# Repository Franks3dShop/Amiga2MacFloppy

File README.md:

# Amiga2MacFloppy
Amiga2MacFloppy, a reversed-engineered A-Max interface

Video of the project from Dr. Dave's Diversions channel, we did this project together:
https://youtu.be/zkYM3wdAgQM?t=42

# General Description

The original A-Max II software allowed to emulate a Macintosh computer on the Amiga and provided an interface (Figure 1) to connect an external Apple floppy drive and use it in emulation. It is also compatible with CrossMAC on the Amiga so you can read Mac floppies on the Amiga.

Amiga2MacFloppy (Figure 2) is a recreation of that board without the Mac ROMs that were required on the original board. It works all the same with a patched version of A-Max II so that it loads the ROMs from file instead.

This interface is designed to receive the IDC connector directly from a 3.5 inch Mac floppy drive or FloppyEmu. You also have the option to the DB19M to IDC adapter (Figure 3) to connect an external Mac floppy drive.

Figure 1-Amax II Interface

Figure 2: The Amiga2MacFloppy Interface

Figure 3 - Adapter DB19M to IDC 2x10

# Software Configuration

## CrossMAC

CrossMAC is Amiga software, consisting of device driver(s) and an
accompanying application, that allows the use of Mac HFS volumes
on the Amiga; the volumes can be mounted, read, and written. This
includes both Mac HFS-formatted 800KB floppy disks and SCSI-attached
Mac HFS hard drive partitions. For floppy disks, of course, some
hardware interface is required to connect the Amiga to a "classic"
Mac-compatible double density floppy drive; Amiga2MacFloppy is
that interface.

Amiga2MacFloppy is known to work with CrossMAC software v1.05 running
on Amiga Release 2.1 system software accompanied by either (a) the
FloppyEmu hardware emulator (in Mac floppy mode; *not* in HD20 mode),
(b) an Apple 3.5 inch double density floppy drive (external DB19
connector), or (c) a Cutting Edge branded 3.5 inch Mac-compatible
double density floppy drive (DB19 connector).

To use CrossMAC with an attached Amiga2MacFloppy, install the
CrossMAC software per its instructions.

## Using CrossMAC

Once CrossMAC installed successfully, HFS-formatted Mac floppy
disks should appear on the Amiga desktop when inserted and can
be accessed much like Amiga FFS volumes.  Launch the CrossMAC
application; this will display the HFS volumes current mounted
and provides Mac-specific HFS volume features such as ejecting
Mac floppy disks and specifying whether Mac HFS files should be
shown in Workbench having Both Forks, Data Fork, or MacBin Only.
split resource and forks.

If you do not have CrossMAC, you can
find it on archive.org in this set of
[CommodoreAmigaApplications](https://archive.org/details/CommodoreAmigaApplicationsADF).

## A-Max

A-Max is the first Macintosh emulator on the Amiga, introduced in
1989. A-Max takes over the entire Amiga when it is running, i.e. does
not multitask with Amiga applications. As such, A-Max II is unique,
amongst Mac emulators on Amiga, in that the entire Amiga is dedicated
to the Mac operations making it fast and highly compatible with
early Mac software when emulating a Macintosh Plus, for example.

Amiga2MacFloppy is known to work with A-Max II software version
2.5 having the "Fast A-Max" patch and running on Amiga Release
2.1 system sofware accompanied by a Mac Plus 128K ROM image file,
and either (a) the FloppyEmu hardware emulator (in Mac floppy mode;
*not* HD20 mode), (b) an Apple 3.5 inch double density floppy drive
(external DB19 connector), or (c) a Cutting Edge branded 3.5 inch
Mac-compatible double density floppy drive (DB19 connector).

To use A-Max II software with an attached Amiga2MacFloppy, you must
use a version of A-Max patched to read the Mac ROM image from a
file rather than from the (2) DIP ROMs that were required in the
original A-Max "cartridge" (an interface that connected to the
Amiga's external floppy disk port) that Amiga2MacFloppy replaces.

The "Fast A-Max" patch modifies the A-Max II software, such as
version 2.5, to read the ROM image from a file called "Mac_ROMs"
in the same directory as the patched A-Max executable. This file
has a format specific to the Fast A-Max patch, but it can be easily
created, e.g. from a 128KB Mac Plus ROMs image file used by other
Mac emulators.  The file simply has a special 32-bit (4 byte)
header; this header contains two 16-bit numbers. The first field
indicates the size of ROM image follows (0x75 for 128KB Mac Plus
ROMs); the second field indicates the drive number or position
where the hardware interface is installed.

For example, a Mac_ROMs image file might begin like this:

	$ hexdump Mac_ROMs |head -1
	0000000 7500 0500 1f4d 7281 4000 2a00 7500 0060
	        ^^^^ ^^^^ ^^^^^^^^^^^^^^^^^^^^^^^^^^^^^
		|    |    |
		|    |    Mac [128KB] ROM image begins here
		|    |
		|    drive number (16-bit value, low byte first) here
		|
		Indicates 128KB (Mac Plus) ROM image follows

Typically, one might install the Amiga2MacFloppy as the second
drive, e.g. the first external drive on an Amiga 500, i.e. `df1:`,
if it were an Amiga floppy drive. In this case, the Mac ROM image
file should indicate the Mac floppy drive has the Amiga floppy drive
number of 4. That is, the ROM image file must specify drive number
4 like this:

	$ hexdump Mac_ROMs |head -1
	0000000 7500 0400 1f4d 7281 4000 2a00 7500 0060
	             ^^^^

Alternatively, one might install the Amgia2MacFloppy as the third
drive, e.g. the first external drive on an Amiga 2000 having two
internal 3.5 inch Amiga floppy drives, i.e. `df2:` if it were an
Amiga floppy drive. In this case, the Mac ROM image file should
indicate the Mac floppy drive has the Amiga floppy drive number of
5. That is the ROM image file must specify drive number 5 like this:

	$ hexdump Mac_ROMs |head -1
	0000000 7500 0500 1f4d 7281 4000 2a00 7500 0060
	             ^^^^

For your convenience, we can make available two Fast A-Max-compatible
ROM image files containing Mac Plus 128KB ROMs and configured
for either of those two floopy drive chain position options; see
Contact info [below](#contact). These are `Mac_ROMs_df1` and `Mac_ROMs_df2`
respectively and you just must copy (or rename) this to a file named
`Mac_ROMs` before starting A-Max II.

Aside: This unusual Mac ROM image file format is necessitated by
the Fast A-Max patch, not by Amiga2MacFloppy, per se. Since the
Fast A-Max patch replaces the portion of A-Max code that finds,
identifies, and loads the external ROMs, this special file header
is used by the patch code to store that necessary information and
convey it to the A-Max software so that A-Max knows the sort of Mac
ROMs supplied (either 64KB or 128KB) and also so that A-Max knows
how to locate the hardware interface to access floppy disks.

Note that if you change the number of Amiga floppy drives positioned
before the Amiga2MacFloppy interface, e.g. if you install an
additional Amiga floppy drive in an Amiga 2000, you will have to
change the Mac ROM image file to one in which the header reflects
the new device number/position of the Amiga2MacFloppy.

# Using A-Max

Most of the use of A-Max is outside the scope of this documentation.
Once properly configured, your Amiga2MacFloppy-connected device will
behave just like a external 800KB drive connected to a classic Mac.
You can even boot Macintosh System software from this external
floppy drive.

In our testing of A-Max II software version 2.5 having the Fast A-Max
patch, we have found no difference between using Amiga2MacFloppy and
using the original A-Max hardware interface. The rare incompatibility
with Macintosh software is likely due to the A-Max emulator, itself,
rather than the floppy drive interface. For example, the original
Microsoft Flight Simulator for the Macintosh is known not to work
with A-Max due to Flight Simulator's heinous requirement that the
original floppy disk must be installed in the internal Macintosh
floppy drive. However, the Mac-compatible floppy drive you attach
when using A-Max always appears as an external floppy drive, thus
it can't be used to run Flight Simulator.

# Dimensions

Figure 4: Dimensions of the Amiga2MacFloppy Board

# PCB Fabrication
You can get the board from PCBWay or any other manifacturer of your choice with the provided gerber zip files.
The default settings from PCBWay should be correct, I prefer to get "HASL lead free" boards to save on the environement https://www.pcbway.com/project/shareproject/Amiga2MacFloppy.html

# Assembly instructions
The PCB fits the 3D printed case provided, You have to center and push the DB23 connectors up to the board, try it first in the case before soldering.

# Revision History
Rev. 1
* Board cleaned up
* OpenHardware Logo added
* Remove the not needed resistor
* Added DB19 and DB23 reference files for KiCAD
* Tested and working

# Contact

Contact Dave via email at the address shared in the
Dr. Dave's Diversions YouTube channel's "About" info:
https://www.youtube.com/c/DrDavesDiversions/about

# LICENCE
©2021 Frank's 3D Shop & Dr. Dave's Diversions

<br />This work is licensed under a <a rel="license" href="http://creativecommons.org/licenses/by/4.0/">Creative Commons Attribution 4.0 International License</a>.

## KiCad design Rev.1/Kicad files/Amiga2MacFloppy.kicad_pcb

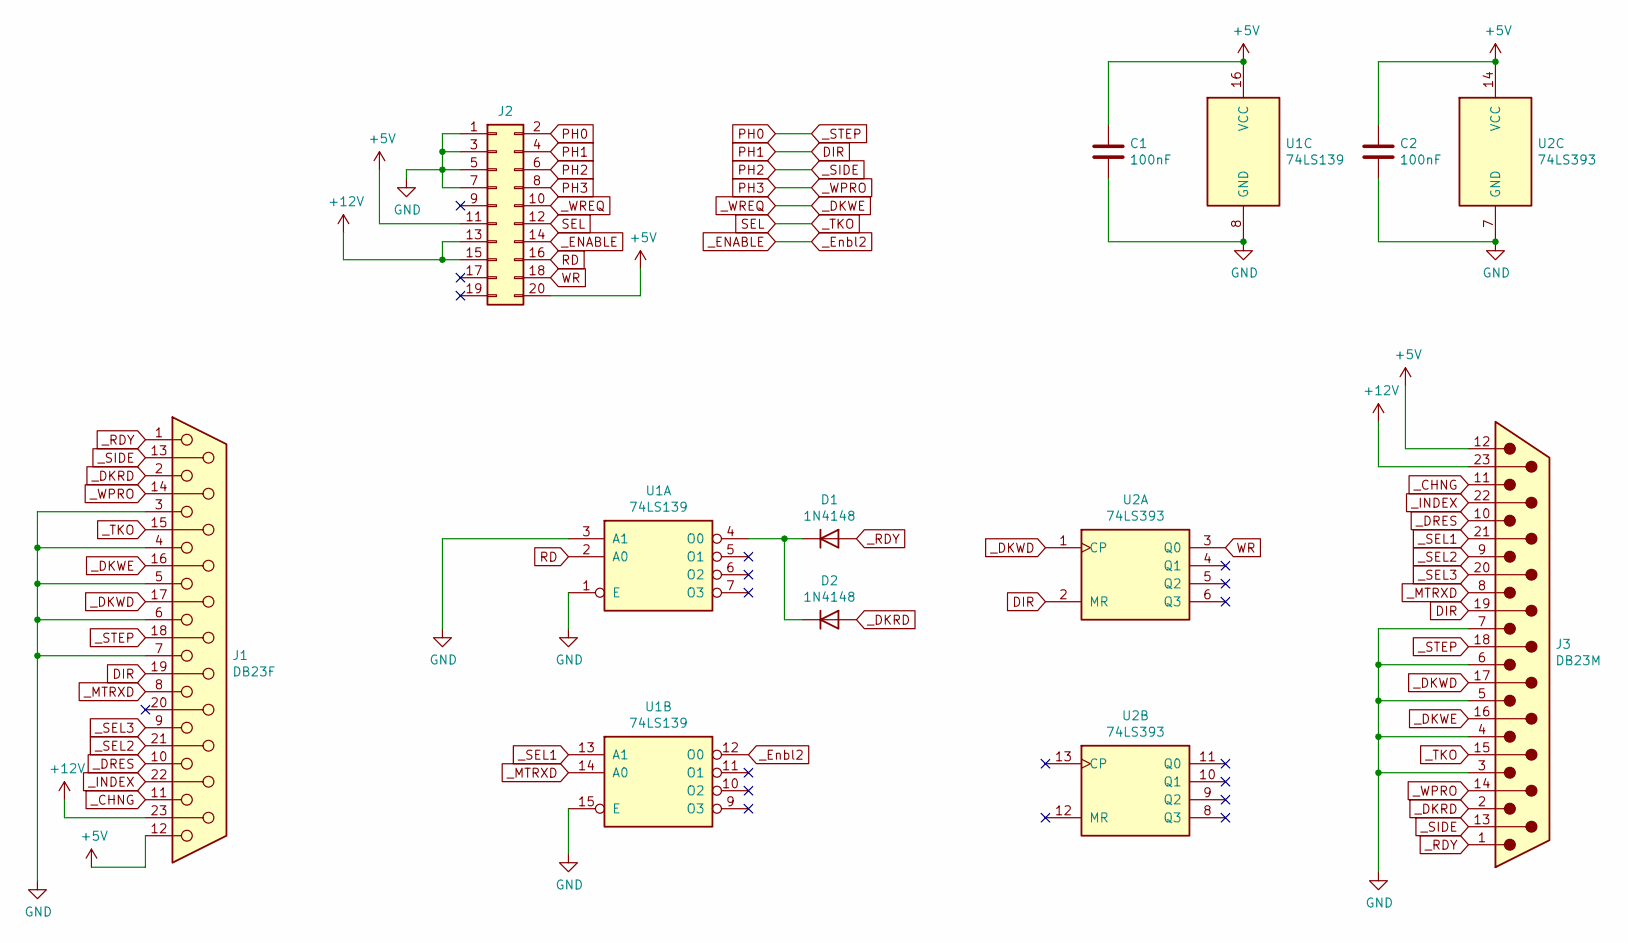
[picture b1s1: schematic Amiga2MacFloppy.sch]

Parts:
C1, C2: 100nF; C_Disc_D7.0mm_W2.5mm_P5.00mm
D1, D2: 1N4148; D_DO-35_SOD27_P7.62mm_Horizontal
J1: DB23F; DSUB-23_Female_EdgeMount_P2.77mm
J2: Conn_02x10_Odd_Even_MountingPin; IDC-Header_2x10_P2.54mm_Vertical
J3: DB23M; DSUB-23_Male_EdgeMount_P2.77mm
U1: 74LS139; DIP-16_W7.62mm
U2: 74LS393; DIP-14_W7.62mm

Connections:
+12V: J1.23, J2.13, J2.15, J3.23
DIR: J1.19, J2.4, J3.19, U2.2 (MR)
GND: C1.2, C2.2, J1.3, J1.4, J1.5, J1.6, J1.7, J2.1, J2.3, J2.5, J2.7, J3.3, J3.4, J3.5, J3.6, J3.7, U1.1 (E), U1.3 (A1), U1.8 (GND), U1.15 (E), U2.7 (GND); also elsewhere on the board
unnamed: D1.1 (K), D2.1 (K), U1.4 (O0)
PH0: J1.18, J2.2, J3.18
PH2: J1.13, J2.6, J3.13
PH3: J1.14, J2.8, J3.14
PWM: C1.1, C2.1, J1.12, J2.11, J2.20, J3.12, U1.16 (VCC), U2.14 (VCC)
RD: J2.16, U1.2 (A0)
SEL: J1.15, J2.12, J3.15
WR: J2.18, U2.3 (Q0)
_CHNG: J1.11, J3.11
_DKRD: D2.2 (A), J1.2, J3.2
_DKWD: J1.17, J3.17, U2.1 (CP)
_DKWE: J1.16, J2.10, J3.16
_DRES: J1.10, J3.10
_ENABLE: J2.14, U1.12 (O0)
_INDEX: J1.22, J3.22
_MTRXD: J1.8, J3.8, U1.14 (A0)
_RDY: D1.2 (A), J1.1, J3.1
_SEL1: J3.21, U1.13 (A1)
_SEL2: J1.21, J3.9; also elsewhere on the board
_SEL3: J1.9, J3.20

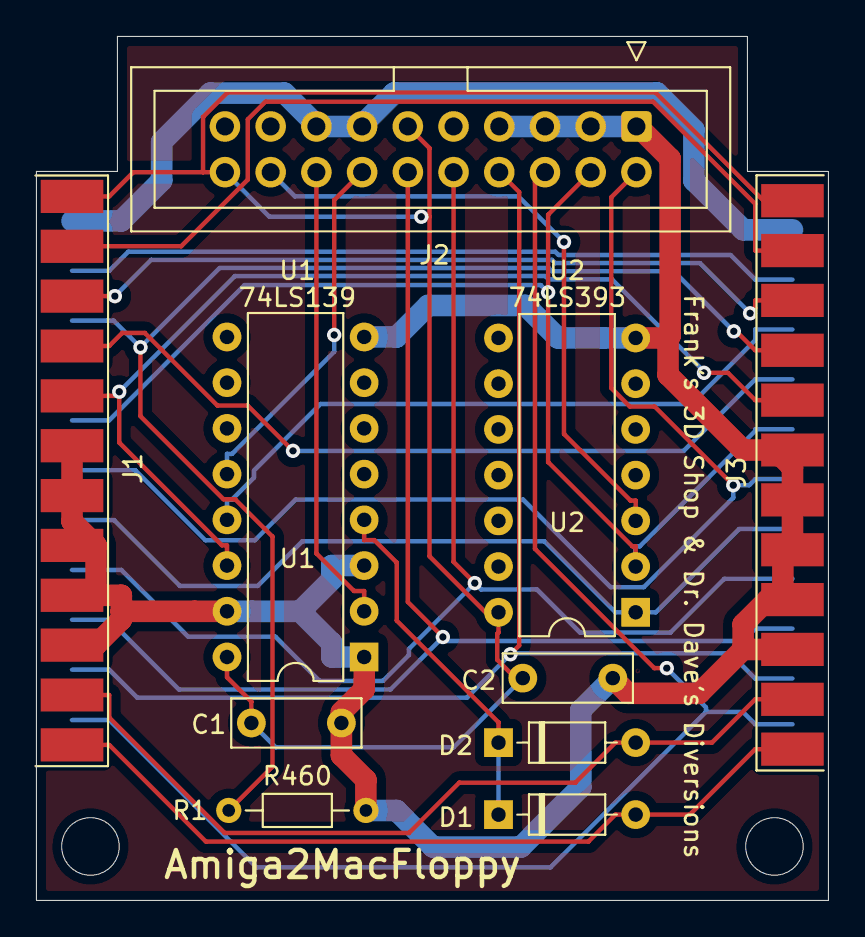
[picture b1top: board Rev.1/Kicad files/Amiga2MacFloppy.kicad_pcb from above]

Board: 2 copper layers, 44.0 x 48.0 mm, 12 parts (0 on the bottom side), 23 nets.

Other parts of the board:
Hole1, Hole2: MountingHole_3.2mm_M3_DIN965
R460: R1; R_Axial_DIN0204_L3.6mm_D1.6mm_P7.62mm_Horizontal

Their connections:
GND: R460.2; also elsewhere on the board
_SEL2: R460.1; also elsewhere on the board

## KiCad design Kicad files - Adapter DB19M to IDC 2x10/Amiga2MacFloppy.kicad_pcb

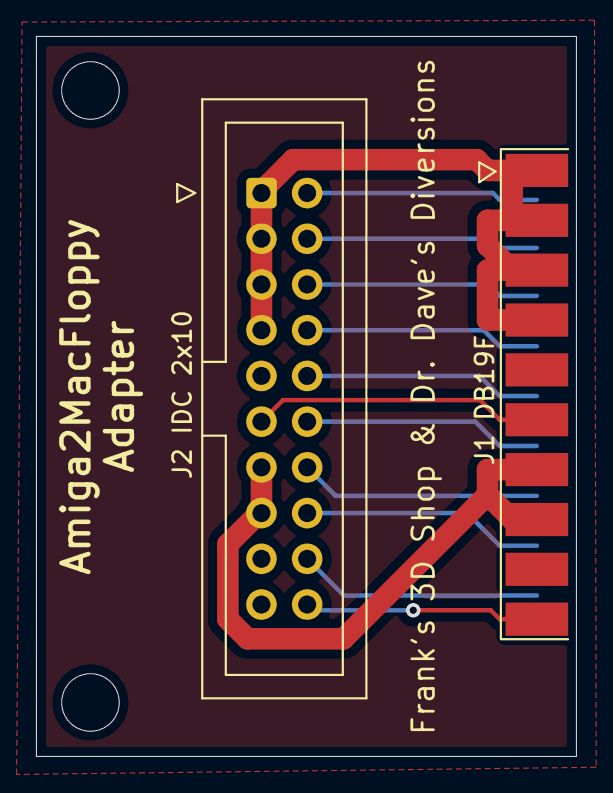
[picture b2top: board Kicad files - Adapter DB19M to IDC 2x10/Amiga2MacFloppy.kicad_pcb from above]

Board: 2 copper layers, 30.0 x 40.0 mm, 5 parts (1 on the bottom side), 13 nets.

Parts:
Hole1, Hole2: MountingHole_3.2mm_M3_DIN965
J1 DB19F: DB19F; DSUB-19_Female_EdgeMount_P2.77mm
J2 IDC 2x10: Conn_02x10_Odd_Even_MountingPin; IDC-Header_2x10_P2.54mm_Vertical
Open Harware Logo BAck: OSHW-Logo2_9.8x8mm_SilkScreen

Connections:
+5V: J1 DB19F.6, J2 IDC 2x10.11
+12V: J1 DB19F.7, J1 DB19F.8, J2 IDC 2x10.13, J2 IDC 2x10.15
DIR: J1 DB19F.12, J2 IDC 2x10.4
GND: J1 DB19F.1, J1 DB19F.2, J1 DB19F.3, J1 DB19F.4, J2 IDC 2x10.1, J2 IDC 2x10.3, J2 IDC 2x10.5, J2 IDC 2x10.7
PH0: J1 DB19F.11, J2 IDC 2x10.2
PH2: J1 DB19F.13, J2 IDC 2x10.6
PH3: J1 DB19F.14, J2 IDC 2x10.8
PWM: J1 DB19F.10, J2 IDC 2x10.20
RD: J1 DB19F.18, J2 IDC 2x10.16
SEL: J1 DB19F.16, J2 IDC 2x10.12
WR: J1 DB19F.19, J2 IDC 2x10.18
_DKWE: J1 DB19F.15, J2 IDC 2x10.10
_ENABLE: J1 DB19F.17, J2 IDC 2x10.14

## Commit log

2021-05-24 First upload
    V1 - Done
    V2 - In progress
2021-05-24 .
    .
2021-05-27 V2
    Modifications done.
    Renamed to the project name.
    Deleted old files.
2021-06-08 Revert to previous version
    .
2021-06-08 Change size
    Changed the size for an Amiga 2000 to clear the RCA mono out jack.
2021-06-08 Smaller Case
2021-06-08 Final touch smaller case
    Amiga 2000 compatible.
2021-06-08 STL
    Added stl of new slimmer case.
2021-06-12 Renamed correctly.
2021-07-05 Added the DB19M to IDC2x10 Adapter
    Adapter to connect Mac Drives via DB19
2021-07-27 Corrections
    Corrected Adapter to Female connector instead of male.
    Removed R1
    Cleaned up schematics
    Added Open Hardware Logo
    Cleaned up silkscreens
2021-07-27 Gerber update
    Updated gerber files with corrections.
2021-07-27 Gerber correction
    Updated Gerber again with new files
2021-07-28 Corrections
    Corrected a missing trace pin 22 of both DB23.
    Updated the Gerber files.
2021-09-15 Doc Draft
    Added documentation draft.
2021-09-15 Moved files
    Made changes to the file structure to make it more standard and added a readme and documentation to be completed later.
2021-09-15 Documentations update
2021-09-15 Update
    Update to board to add dimension and export it into the doc.
2021-09-15 Update README.md
    Added OpenHardware notice.
2021-09-15 LICENCE
2021-09-16 Added STL fot the case
    3D Printed case added
2021-09-16 Added Dr.Dave Diversion's video explanation.
2021-09-16 Updated attributions.
2021-09-16 Creative Comons
    Modified for CC licence
2021-09-16 Small update
2022-03-17 PDF of doc
    Added a pdf version of the Word documentation...
2022-09-26 fixed typos
2022-09-27 fixed typos; added info about running software
2022-09-27 fixed typo
2022-09-27 made "CrossMAC" (caps) consistent
2022-09-27 typo fix
2022-09-27 added contact info
2022-09-27 rewording
